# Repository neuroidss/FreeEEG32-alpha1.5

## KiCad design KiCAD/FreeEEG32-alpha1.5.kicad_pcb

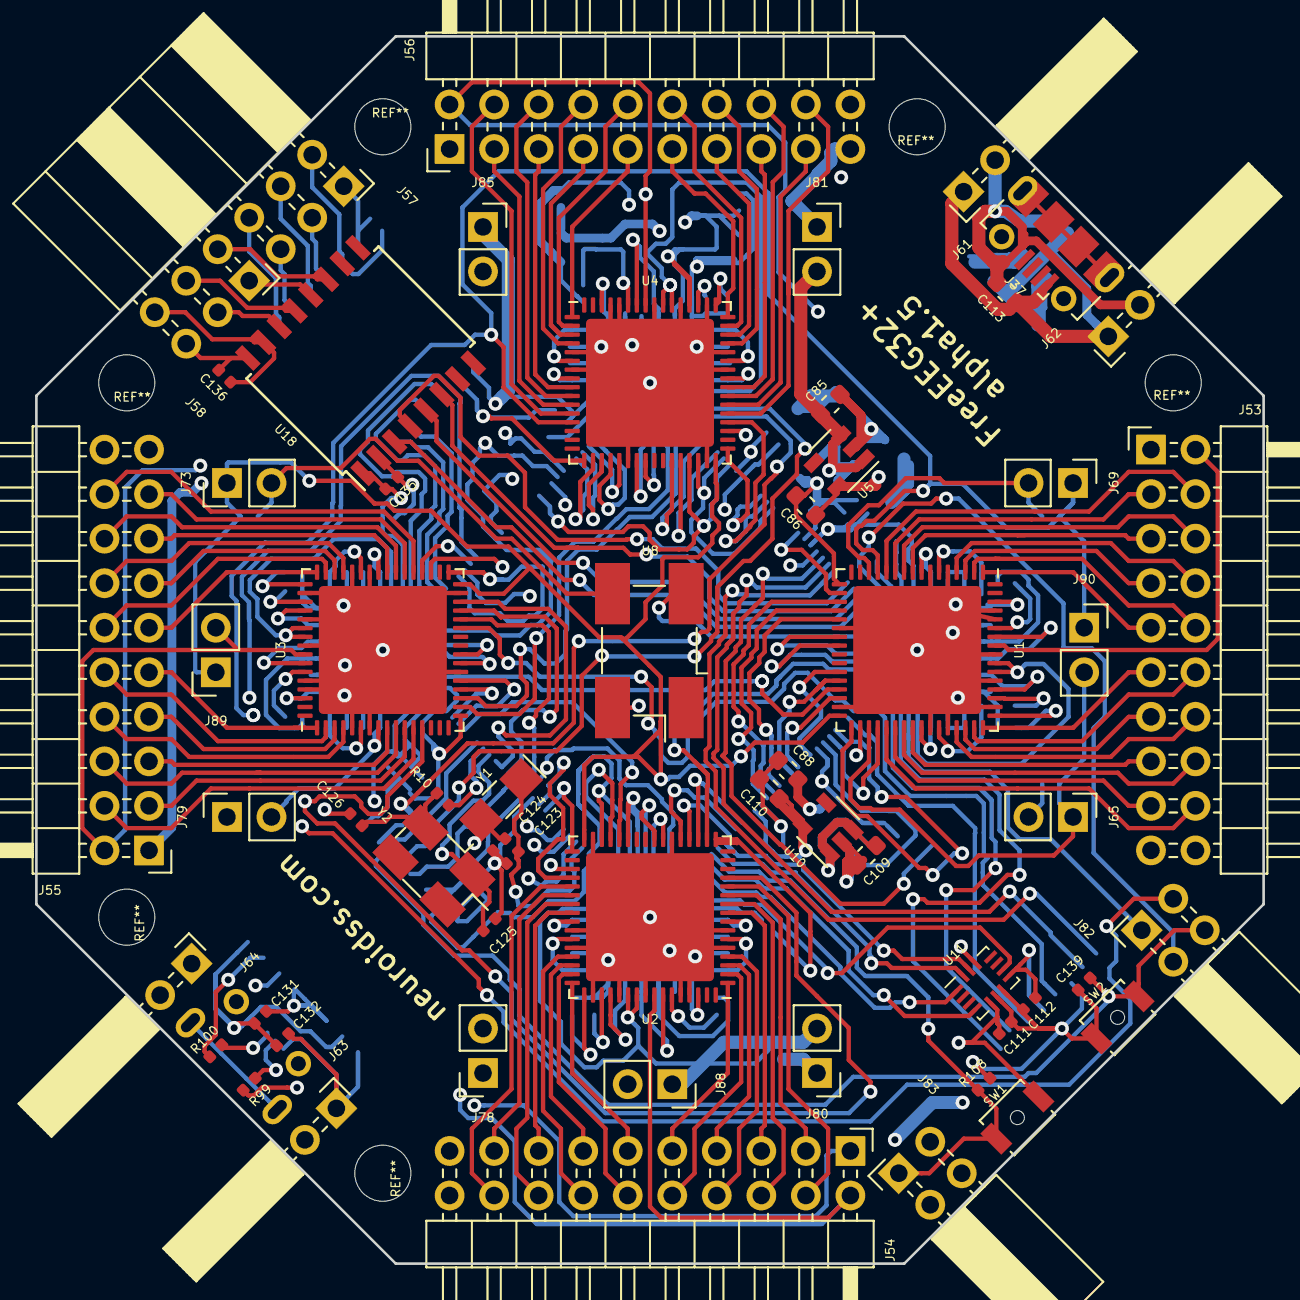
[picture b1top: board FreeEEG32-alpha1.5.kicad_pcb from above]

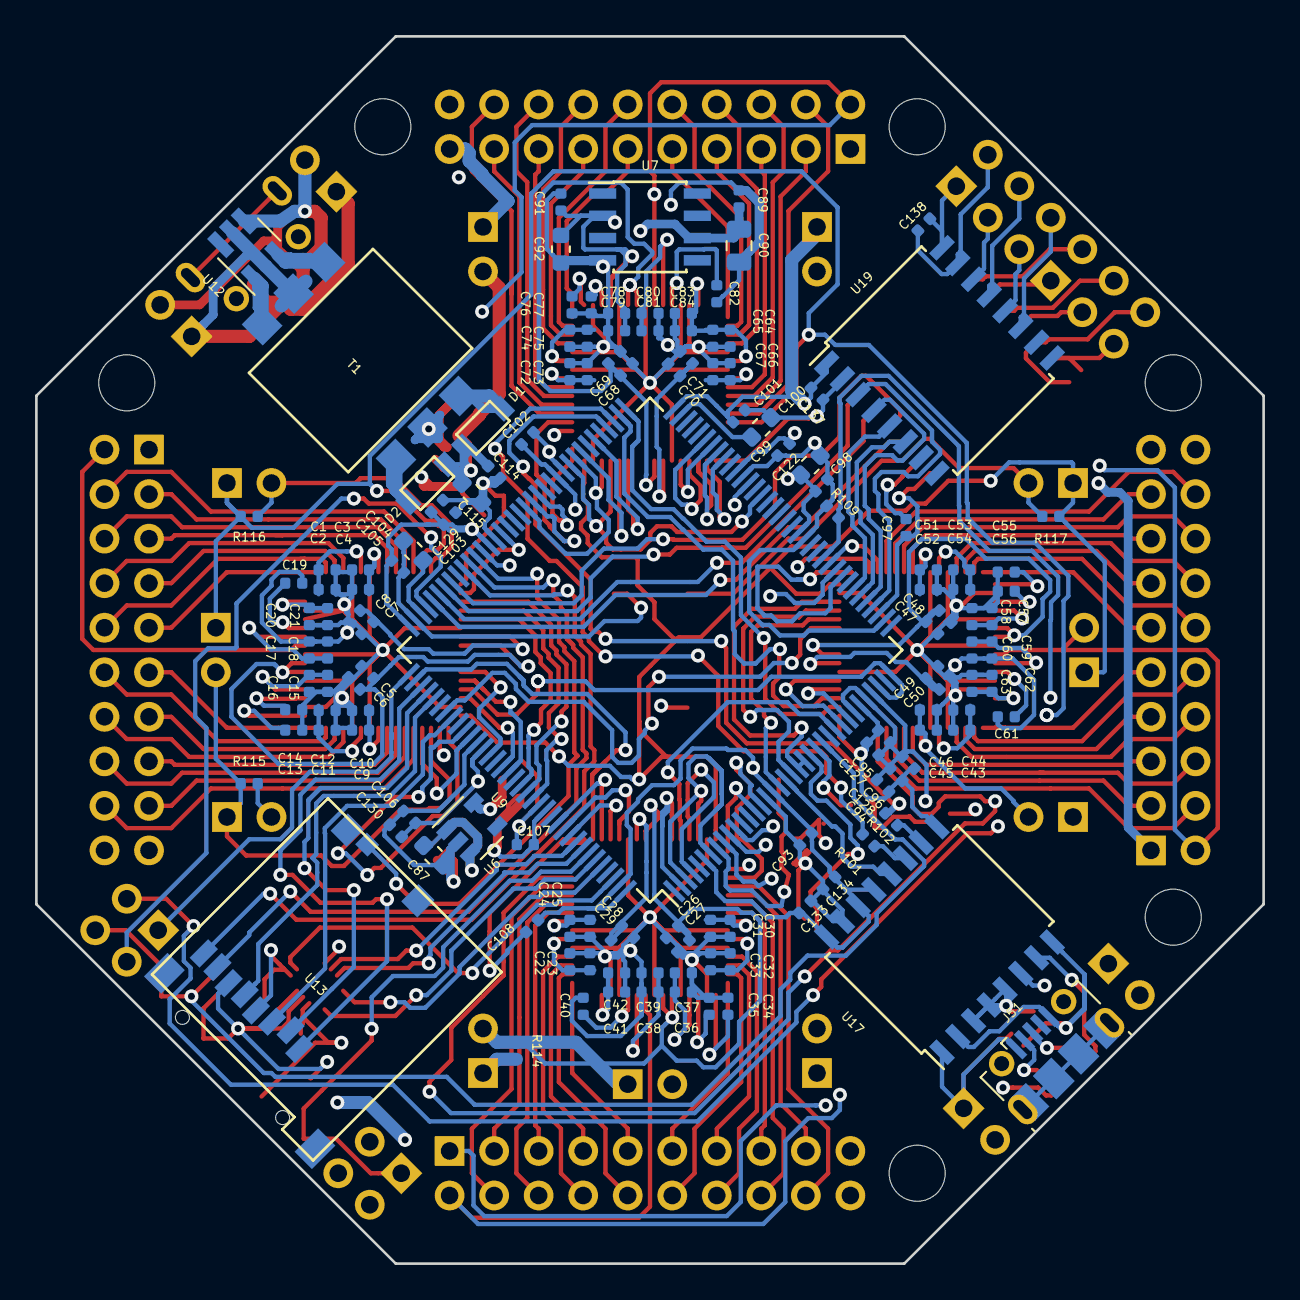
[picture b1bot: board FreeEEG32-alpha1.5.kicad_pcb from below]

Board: 4 copper layers, 70.0 x 70.0 mm, 192 parts (134 on the bottom side), 199 nets.

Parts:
C1, C3, C5, C7, C9, C11, C13, C14, C15, C17, C19, C20, C22, C24, C26, C28, C30, C32, C34, C35, C36, C38, C40, C41, C43, C45, C47, C49, C51, C53, C55, C56, C57, C59, C61, C62, C64, C66, C68, C70, C72, C74, C76, C77, C78, C80, C82, C83, C89, C91, C93, C94, C95, C96, C97, C98, C99, C101, C102, C103, C105, C106, C107, C108, C111, C112, C114, C131, C132, C133, C134, C135, C136, C137, C138, C139: 100n; C_0402_1005Metric
C2, C4, C6, C8, C10, C12, C16, C18, C21, C23, C25, C27, C29, C31, C33, C37, C39, C42, C44, C46, C48, C50, C52, C54, C58, C60, C63, C65, C67, C69, C71, C73, C75, C79, C81, C84, C127, C128, C129, C130: 1u; C_0402_1005Metric
C85, C86, C87, C88, C100, C104, C109, C110: 2.2u; C_0603_1608Metric
C90: 22u; C_0805_2012Metric
C92, C113, C115: 10u; C_0603_1608Metric
C122: 4.7u; C_0603_1608Metric
C123, C125: CL1; C_0402_1005Metric
C124, C126: CL2; C_0402_1005Metric
D1, D2: D_Schottky; SOD−123
J37, J51: USB_B_Micro; USB_Micro-B_Molex-105017-0001
J53, J54, J55, J56: Conn_02x10_Odd_Even; PinHeader_2x10_P2.54mm_Horizontal
J57, J58: Conn_02x03_Odd_Even; PinSocket_2x03_P2.54mm_Horizontal
J61, J62, J63, J64: Conn_01x02; PinSocket_2x01_P2.54mm_Horizontal
J65, J69, J73, J80: Conn_01x02; PinHeader_1x02_P2.54mm_Vertical
J78, J79, J81, J85, J88, J89, J90: Conn_01x02; PinSocket_1x02_P2.54mm_Vertical
J82, J83: Conn_02x02_Odd_Even; PinSocket_2x02_P2.54mm_Horizontal
R10: R_EXT; R_0402_1005Metric
R99, R100, R101, R102: 20; R_0402_1005Metric
R108, R109: 4k7; R_0402_1005Metric
R114, R115, R116, R117: 0; R_0402_1005Metric
SW1, SW2: SW_Push; SW_SPST_B3U-1000P-B
T1: da2303; 750315371
U1, U2, U3, U4: AD7779; QFN-64-1EP_9x9mm_P0.5mm_EP7.3x7.3mm
U5, U6, U10: LP5907; SOT-23-5
U7: ADR4525; SOIC-8_3.9x4.9mm_P1.27mm
U8: FXO-SM7_OSC-SMD7050_short; Oscillator_SMD_EuroQuartz_XO91-4Pin_7.0x5.0mm_HandSoldering
U9: STM32F765ZITx; LQFP-144_20x20mm_P0.5mm
U11: LSM6DS3; Bosch_LGA-14_3x2.5mm_P0.5mm
U12: SN6505A; SOT-23-6_Handsoldering
U13: 473521001
U17: ADuM3160; SOIC-16W_7.5x10.3mm_P1.27mm
U18: ADUM1402BRWZ; SOIC-16W_7.5x10.3mm_P1.27mm
U19: ISO7341c; SOIC-16W_7.5x10.3mm_P1.27mm
Y1: 32768Hz; Crystal_SMD_EuroQuartz_EQ161-2Pin_3.2x1.5mm_HandSoldering
Y2: 16MHz; Crystal_SMD_EuroQuartz_MJ-4Pin_5.0x3.2mm_HandSoldering

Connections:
/ADC1/1_AIN0-: J53.9, U1.1
/ADC1/2_AIN0+: J53.10, U1.2
/ADC1/3_AIN1-: J53.7, U1.3
/ADC1/4_AIN1+: J53.8, U1.4
/ADC1/9_AIN2-: J53.5, U1.9
/ADC1/10_AIN2+: J53.6, U1.10
/ADC1/11_AIN3-: J53.3, U1.11
/ADC1/12_AIN3+: J53.4, U1.12
/ADC1/37_AIN7+: J53.18, U1.37
/ADC1/38_AIN7-: J53.17, U1.38
/ADC1/39_AIN6+: J53.16, U1.39
/ADC1/40_AIN6-: J53.15, U1.40
/ADC1/45_AIN5+: J53.14, U1.45
/ADC1/46_AIN5-: J53.13, U1.46
/ADC1/47_AIN4+: J53.12, U1.47
/ADC1/48_AIN4-: J53.11, U1.48
/ADC1/49_REF_OUT: C13.1, U1.49
/ADC1/51_AREG2CAP: C14.1, U1.51
/ADC1/59_AREG1CAP: C19.1, U1.59
/ADC2/1_AIN0-: J54.9, U2.1
/ADC2/2_AIN0+: J54.10, U2.2
/ADC2/3_AIN1-: J54.7, U2.3
/ADC2/4_AIN1+: J54.8, U2.4
/ADC2/9_AIN2-: J54.5, U2.9
/ADC2/10_AIN2+: J54.6, U2.10
/ADC2/11_AIN3-: J54.3, U2.11
/ADC2/12_AIN3+: J54.4, U2.12
/ADC2/37_AIN7+: J54.18, U2.37
/ADC2/38_AIN7-: J54.17, U2.38
/ADC2/39_AIN6+: J54.16, U2.39
/ADC2/40_AIN6-: J54.15, U2.40
/ADC2/45_AIN5+: J54.14, U2.45
/ADC2/46_AIN5-: J54.13, U2.46
/ADC2/47_AIN4+: J54.12, U2.47
/ADC2/48_AIN4-: J54.11, U2.48
/ADC2/49_REF_OUT: C34.1, U2.49
/ADC2/51_AREG2CAP: C35.1, U2.51
/ADC2/59_AREG1CAP: C40.1, U2.59
/ADC3/1_AIN0-: J55.9, U3.1
/ADC3/2_AIN0+: J55.10, U3.2
/ADC3/3_AIN1-: J55.7, U3.3
/ADC3/4_AIN1+: J55.8, U3.4
/ADC3/9_AIN2-: J55.5, U3.9
/ADC3/10_AIN2+: J55.6, U3.10
/ADC3/11_AIN3-: J55.3, U3.11
/ADC3/12_AIN3+: J55.4, U3.12
/ADC3/37_AIN7+: J55.18, U3.37
/ADC3/38_AIN7-: J55.17, U3.38
/ADC3/39_AIN6+: J55.16, U3.39
/ADC3/40_AIN6-: J55.15, U3.40
/ADC3/45_AIN5+: J55.14, U3.45
/ADC3/46_AIN5-: J55.13, U3.46
/ADC3/47_AIN4+: J55.12, U3.47
/ADC3/48_AIN4-: J55.11, U3.48
/ADC3/49_REF_OUT: C55.1, U3.49
/ADC3/51_AREG2CAP: C56.1, U3.51
/ADC3/59_AREG1CAP: C61.1, U3.59
/ADC4/37_AIN7+: J56.18, U4.37
/ADC4/38_AIN7-: J56.17, U4.38
/ADC4/39_AIN6+: J56.16, U4.39
/ADC4/40_AIN6-: J56.15, U4.40
/ADC4/45_AIN5+: J56.14, U4.45
/ADC4/46_AIN5-: J56.13, U4.46
/ADC4/47_AIN4+: J56.12, U4.47
/ADC4/48_AIN4-: J56.11, U4.48
/ADC4/49_REF_OUT: C76.1, U4.49
/ADC4/51_AREG2CAP: C77.1, U4.51
/ADC4/59_AREG1CAP: C82.1, U4.59
/MCU/8_PC14: C123.1, U9.8, Y1.1
/MCU/9_PC15: C124.1, U9.9, Y1.2
/MCU/23_PH0: C125.1, U9.23, Y2.1
/MCU/24_PH1: R10.1, U9.24
/MCU/71_VCAP_1: C100.1, U9.71
/MCU/106_VCAP_2: C104.1, U9.106
ACC_1_SDO_SAO: U9.140, U11.1
ACC_4_INT1: U9.139, U11.4
ACC_6_GND: C1.1, C2.1, C3.1, C4.1, C5.1, C6.1, C7.1, C8.1, C9.1, C10.1, C11.1, C12.1, C13.2, C14.2, C15.1, C16.1, C17.1, C18.1, C19.2, C20.2, C21.2, C22.1, C23.1, C24.1, C25.1, C26.1, C27.1, C28.1, C29.1, C30.1, C31.1, C32.1, C33.1, C34.2, C35.2, C36.1, C37.1, C38.1, C39.1, C40.2, C41.2, C42.2, C43.1, C44.1, C45.1, C46.1, C47.1, C48.1, C49.1, C50.1, C51.1, C52.1, C53.1, C54.1, C55.2, C56.2, C57.1, C58.1, C59.1, C60.1, C61.2, C62.2, C63.2, C64.1, C65.1, C66.1, C67.1, C68.1, C69.1, C70.1, C71.1, C72.1, C73.1, C74.1, C75.1, C76.2, C77.2, C78.1, C79.1, C80.1, C81.1, C82.2, C83.2, C84.2, C85.2, C86.2, C87.2, C88.2, C89.2, C90.2, C91.2, C92.2, C93.2, C94.2, C95.2, C96.2, C97.2, C98.2, C99.2, C100.2, C101.2, C102.2, C103.2, C104.2, C105.2, C106.2, C107.2, C108.2, C109.2, C110.2, C111.2, C112.2, C114.2, C115.2, C122.2, C123.2, C124.2, C125.2, C126.2, C127.2, C128.2, C129.2, C130.2, C133.2, C134.2, C135.2, C137.2, C139.1, J53.19, J54.19, J55.19, J56.19, J79.1, J81.1, J83.4, R108.2, R109.2, SW2.1, T1.7, U1.5, U1.7, U1.17, U1.22, U1.31, U1.42, U1.44, U1.50, U1.53, U1.56, U1.60, U1.61, U1.65, U2.5, U2.7, U2.17, U2.22, U2.31, U2.42, U2.44, U2.50, U2.53, U2.56, U2.60, U2.61, U2.65, U3.5, U3.7, U3.17, U3.22, U3.31, U3.42, U3.44, U3.50, U3.53, U3.56, U3.60, U3.61, U3.65, U4.5, U4.7, U4.17, U4.22, U4.31, U4.42, U4.44, U4.50, U4.53, U4.56, U4.60, U4.61, U4.65, U5.2, U6.2, U7.4, U8.2, U9.16, U9.31, U9.38, U9.51, U9.61, U9.83, U9.94, U9.107, U9.120, U9.130, U10.2, U11.6, U11.7, U13.6, U17.9, U17.15, U18.2, U19.2
ACC_9_INT2: U9.142, U11.9
ACC_12_CS: C93.1, C94.1, C95.1, C96.1, C97.1, C98.1, C99.1, C101.1, C102.1, C103.1, C105.1, C106.1, C107.1, C108.1, C110.1, C111.1, C112.1, C122.1, C127.1, C128.1, C129.1, C130.1, C133.1, C134.1, C135.1, C137.1, J83.3, J85.1, SW1.1, U9.6, U9.17, U9.30, U9.32, U9.33, U9.39, U9.52, U9.62, U9.72, U9.84, U9.95, U9.108, U9.121, U9.131, U9.143, U9.144, U10.5, U11.5, U11.8, U11.12, U13.4, U17.13, U17.14, U17.16, U18.1, U19.1
ACC_13_SCL: U9.136, U11.13
ACC_14_SDA: U9.137, U11.14
ADC1_13_MODE0_GPIO0: J69.1, J90.1, R116.2, U1.13, U2.13, U3.13, U4.13
ADC1_14_MODE1_GPIO1: J69.2, R116.1, U1.14
ADC1_18_ALERT_CS: U1.18, U9.93
ADC1_19_DCLK2_SCLK: U1.19, U9.128
ADC1_20_DCLK1_SDI: U1.20, U9.129
ADC1_21_DCLK0_SDO: U1.21, U9.127
ADC1_23_DREGCAP: C7.2, C8.2, U1.23
ADC1_24_IOVDD: C5.2, C6.2, C26.2, C27.2, C47.2, C48.2, C68.2, C69.2, C88.1, J80.2, J88.1, R114.1, U1.24, U1.54, U1.55, U2.24, U2.54, U2.55, U3.24, U3.54, U3.55, U4.24, U4.54, U4.55, U6.5
ADC1_27_DOUT1: U1.27, U9.122
ADC1_28_DOUT0: U1.28, U9.125
ADC1_29_DCLK: U1.29, U9.34, U9.36
ADC1_30_DRDY: U1.30, U9.46, U9.96, U9.124
ADC1_32_XTAL2_MCLK: J73.1, J89.1, R117.2, U1.32, U2.32, U3.32, U4.32
ADC1_33_START: U1.33, U9.118
ADC1_34_SYNC_OUT: J65.2, R115.1, U1.34
ADC1_35_SYNC_IN: J65.1, J90.2, R115.2, U1.35, U2.35, U3.35, U4.35
ADC1_36_RESET: U1.36, U9.119
ADC1_41_REF2+: C3.2, C4.2, C9.2, C10.2, C24.2, C25.2, C30.2, C31.2, C45.2, C46.2, C51.2, C52.2, C66.2, C67.2, C72.2, C73.2, C89.1, C90.1, J79.2, U1.8, U1.41, U2.8, U2.41, U3.8, U3.41, U4.8, U4.41, U7.6
ADC1_43_AVDD1B: C1.2, C2.2, C11.2, C12.2, C15.2, C16.2, C17.2, C18.2, C20.1, C21.1, C22.2, C23.2, C32.2, C33.2, C36.2, C37.2, C38.2, C39.2, C41.1, C42.1, C43.2, C44.2, C53.2, C54.2, C57.2, C58.2, C59.2, C60.2, C62.1, C63.1, C64.2, C65.2, C74.2, C75.2, C78.2, C79.2, C80.2, C81.2, C83.1, C84.1, C86.1, C91.1, C92.1, J53.20, J54.20, J55.20, J56.20, J85.2, U1.6, U1.43, U1.52, U1.58, U1.62, U2.6, U2.43, U2.52, U2.58, U2.62, U3.6, U3.43, U3.52, U3.58, U3.62, U4.6, U4.43, U4.52, U4.58, U4.62, U5.5, U7.2
ADC1_57_VCM: J53.2, J54.2, J55.2, J56.2, J89.2, U1.57, U2.57, U3.57, U4.57
ADC2_18_ALERT_CS: U2.18, U9.110
ADC2_19_DCLK2_SCLK: U2.19, U9.133
ADC2_20_DCLK1_SDI: U2.20, U9.135
ADC2_21_DCLK0_SDO: U2.21, U9.134
ADC2_23_DREGCAP: C28.2, C29.2, U2.23
ADC2_27_DOUT1: U2.27, U9.2
ADC2_28_DOUT0: U2.28, U9.27
ADC2_29_DCLK: U2.29, U9.4
ADC2_30_DRDY: U2.30, U9.3, U9.7
ADC2_33_START: U2.33, U9.14
ADC2_36_RESET: U2.36, U9.15
ADC3_18_ALERT_CS: U3.18, U9.73
ADC3_19_DCLK2_SCLK: U3.19, U9.74
ADC3_20_DCLK1_SDI: U3.20, U9.29
ADC3_21_DCLK0_SDO: U3.21, U9.28
ADC3_23_DREGCAP: C49.2, C50.2, U3.23
ADC3_27_DOUT1: U3.27, U9.115
ADC3_28_DOUT0: U3.28, U9.18
ADC3_29_DCLK: U3.29, U9.20
ADC3_30_DRDY: U3.30, U9.21, U9.22
ADC3_33_START: U3.33, U9.45
ADC3_36_RESET: U3.36, U9.47
ADC4_18_ALERT_CS: U4.18, U9.64
ADC4_19_DCLK2_SCLK: U4.19, U9.65
ADC4_20_DCLK1_SDI: U4.20, U9.67
ADC4_21_DCLK0_SDO: U4.21, U9.66
ADC4_23_DREGCAP: C70.2, C71.2, U4.23
ADC4_27_DOUT1: U4.27, U9.78
ADC4_28_DOUT0: U4.28, U9.80
ADC4_29_DCLK: U4.29, U9.58, U9.82
ADC4_30_DRDY: U4.30, U9.60, U9.81, U9.89
ADC4_33_START: U4.33, U9.87
ADC4_36_RESET: U4.36, U9.88
ADC4_AIN0+: J56.10, U4.2
ADC4_AIN0-: J56.9, U4.1
ADC4_AIN1+: J56.8, U4.4
ADC4_AIN1-: J56.7, U4.3
ADC4_AIN2+: J56.6, U4.10
ADC4_AIN2-: J56.5, U4.9
ADC4_AIN3+: J56.4, U4.12
ADC4_AIN3-: J56.3, U4.11
AINREF-: J53.1, J54.1, J55.1, J56.1, J88.2
AVDD_1_IN: C85.1, C87.1, C109.1, C114.1, C115.1, D1.1, D2.1, J81.2, J83.2, U5.1, U5.3, U6.1, U6.3, U10.1, U10.3
CRYSTAL_3_OUT: J73.2, R117.1, U8.3
CRYSTAL_4_Vin: J80.1, R114.2, U8.4
ISO_SPI_3_INA: U9.40, U19.3
ISO_SPI_4_INB: U9.41, U19.4
ISO_SPI_5_INC: U9.43, U19.5
ISO_SPI_6_OUTD: U9.42, U19.6
ISO_SPI_11_IND: J57.6, U19.11
ISO_SPI_12_OUTC: J57.5, U19.12
ISO_SPI_13_OUTB: J57.4, U19.13
ISO_SPI_14_OUTA: J57.3, U19.14
ISO_SPI_15_GND2: C138.2, J57.2, U19.15
ISO_SPI_16_VCC2: C138.1, J57.1, U19.16
ISO_UART_3_INA: U9.104, U18.3
ISO_UART_4_INB: U9.101, U18.4
ISO_UART_5_OUTC: U9.103, U18.5
ISO_UART_6_OUTD: U9.102, U18.6
ISO_UART_11_IND: J58.2, U18.11
ISO_UART_12_INC: J58.1, U18.12
ISO_UART_13_OUTB: J58.4, U18.13
ISO_UART_14_OUTA: J58.3, U18.14
ISO_UART_15_GND2: C136.2, J58.6, U18.15
ISO_UART_16_VCC2: C136.1, J58.5, U18.16
ISO_USB_1_VBUS1: C132.1, J51.1, J63.1, U17.1
ISO_USB_2_GND1: C131.2, C132.2, J51.5, J63.2, U17.2, U17.8
ISO_USB_3_VDD1: C131.1, U17.3, U17.4, U17.5
ISO_USB_6_UD–: J51.2, J64.2, R99.2
ISO_USB_7_UD+: J51.3, J64.1, R100.2
ISO_USB_10_DD+: R102.1, U9.76
ISO_USB_11_DD–: R101.1, U9.75
ISO_USB_12_PIN: U9.19, U17.12
MCU_10_PF0_I2C2_SDA: J78.2, U9.10
MCU_11_PF1_I2C2_SCL: J78.1, U9.11
MCU_25_NRST: C139.2, J82.4, SW2.2, U9.25
MCU_48_PB2_BOOT1: J82.3, R109.1, U9.48
MCU_97_PC7_SDMMC1_DETECT: U9.97, U13.9
MCU_98_PC8_SDMMC1_D0: U9.98, U13.7
MCU_99_PC9_SDMMC1_D1: U9.99, U13.8
MCU_105_PA13_SYS_JTMS-SWDIO: J82.2, U9.105
MCU_109_PA14_SYS_JTCK-SWCLK: J82.1, U9.109
MCU_111_PC10_SDMMC1_D2: U9.111, U13.1
MCU_112_PC11_SDMMC1_D3: U9.112, U13.2
MCU_113_PC12_SDMMC1_CK: U9.113, U13.5
MCU_116_PD2_SDMMC1_CMD: U9.116, U13.3
MCU_138_BOOT0: J83.1, R108.1, SW1.2, U9.138
unnamed: C126.1, R10.2, Y2.2
unnamed: D1.2, T1.8
unnamed: D2.2, T1.5
unnamed: R99.1, U17.6
unnamed: R100.1, U17.7
unnamed: R101.2, U17.11
unnamed: R102.2, U17.10
unnamed: T1.1, U12.3
unnamed: T1.4, U12.1
POWER_1_GND: C113.1, J37.5, J61.2, J62.2, U12.4
POWER_2_VCC: C113.2, J37.1, J61.1, J62.1, T1.2, U12.2, U12.5

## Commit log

2022-03-20 freeeeg32-alpha131 & freeeeg128-alpha
